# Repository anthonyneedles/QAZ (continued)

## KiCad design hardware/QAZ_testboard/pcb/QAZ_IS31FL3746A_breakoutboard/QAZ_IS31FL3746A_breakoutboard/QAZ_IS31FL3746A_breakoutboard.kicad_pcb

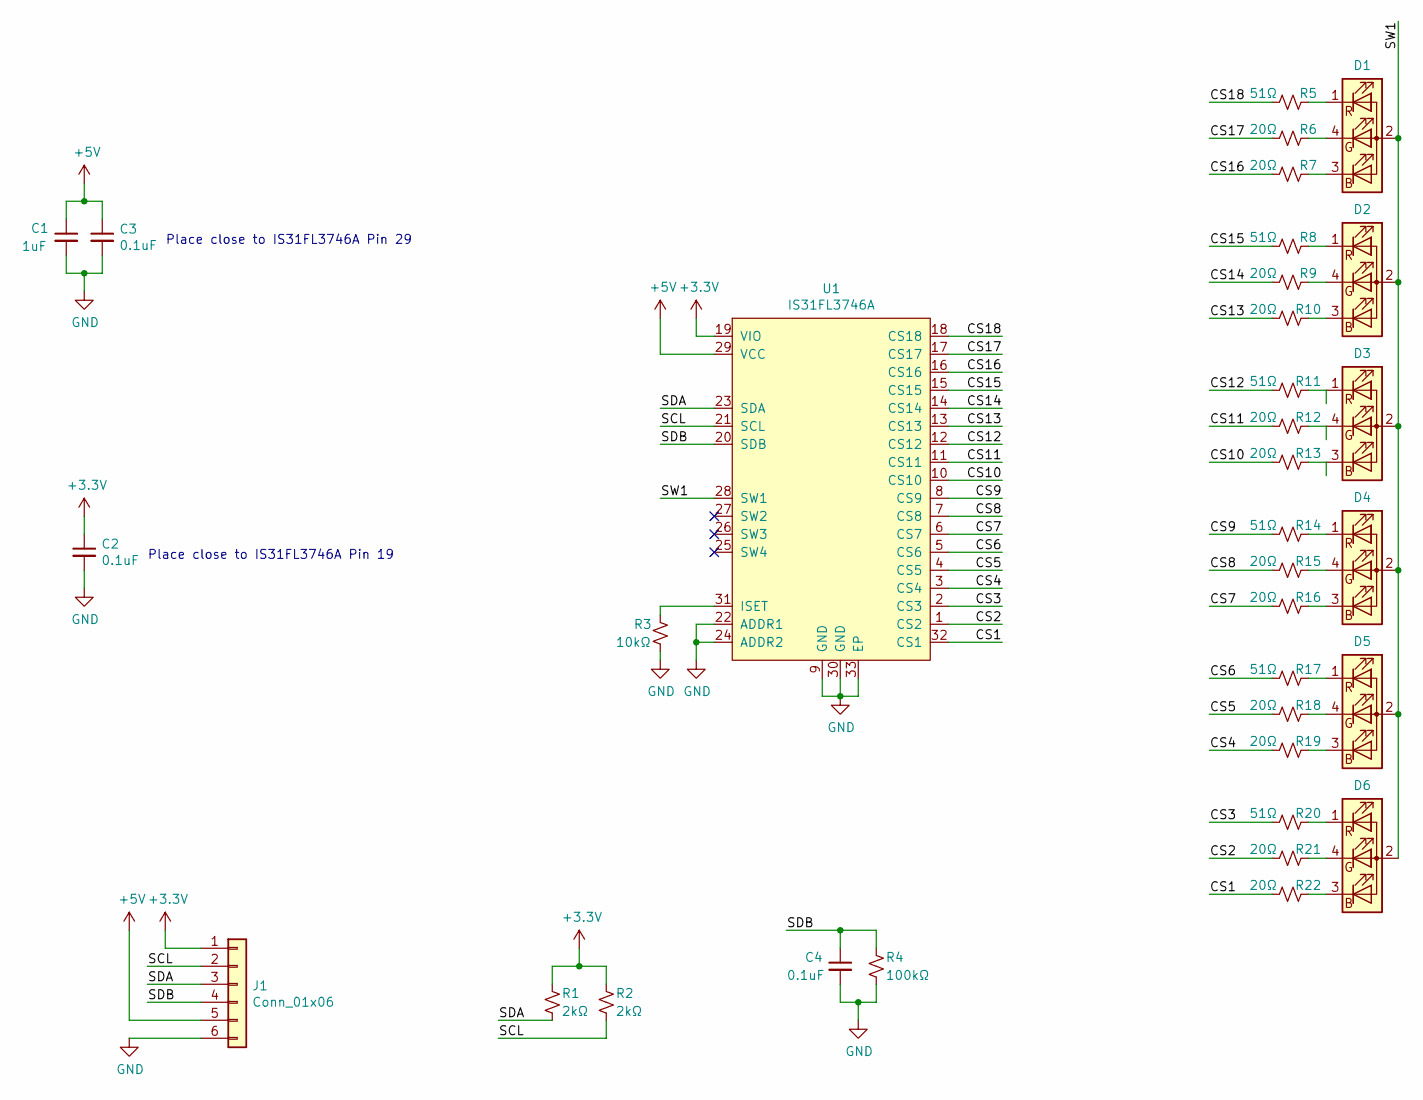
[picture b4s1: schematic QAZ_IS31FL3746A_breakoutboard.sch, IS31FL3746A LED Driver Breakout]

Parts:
C1: 1uF; C_0603_1608Metric_Pad1.05x0.95mm_HandSolder
C2, C3, C4: 0.1uF; C_0603_1608Metric_Pad1.05x0.95mm_HandSolder
D1, D2, D3, D4, D5, D6: LED_ARGB; LED_D5.0mm-4_RGB
J1: Conn_01x06; PinHeader_1x06_P2.54mm_Vertical
R1, R2: 2kΩ; R_0603_1608Metric_Pad1.05x0.95mm_HandSolder
R3: 10kΩ; R_0603_1608Metric_Pad1.05x0.95mm_HandSolder
R4: 100kΩ; R_0603_1608Metric_Pad1.05x0.95mm_HandSolder
R5, R8, R11, R14, R17, R20: 51Ω; R_0603_1608Metric_Pad1.05x0.95mm_HandSolder
R6, R7, R9, R10, R12, R13, R15, R16, R18, R19, R21, R22: 20Ω; R_0603_1608Metric_Pad1.05x0.95mm_HandSolder
U1: IS31FL3746A; QFN-32-1EP_4x4mm_P0.4mm_EP2.9x2.9mm_HS

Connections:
+3V3: C2.1, J1.1, R1.1, R2.1, U1.19 (VIO)
+5V: C1.1, C3.1, J1.5, U1.29 (VCC)
/CS1: R22.2, U1.32 (CS1)
/CS2: R21.2, U1.1 (CS2)
/CS3: R20.2, U1.2 (CS3)
/CS4: R19.2, U1.3 (CS4)
/CS5: R18.2, U1.4 (CS5)
/CS6: R17.2, U1.5 (CS6)
/CS7: R16.2, U1.6 (CS7)
/CS8: R15.2, U1.7 (CS8)
/CS9: R14.2, U1.8 (CS9)
/CS10: R13.2, U1.10 (CS10)
/CS11: R12.2, U1.11 (CS11)
/CS12: R11.2, U1.12 (CS12)
/CS13: R10.2, U1.13 (CS13)
/CS14: R9.2, U1.14 (CS14)
/CS15: R8.2, U1.15 (CS15)
/CS16: R7.2, U1.16 (CS16)
/CS17: R6.2, U1.17 (CS17)
/CS18: R5.2, U1.18 (CS18)
/SCL: J1.2, R2.2, U1.21 (SCL)
/SDA: J1.3, R1.2, U1.23 (SDA)
/SDB: C4.1, J1.4, R4.1, U1.20 (SDB)
/SW1: D1.2 (A), D2.2 (A), D3.2 (A), D4.2 (A), D5.2 (A), D6.2 (A), U1.28 (SW1)
GND: C1.2, C2.2, C3.2, C4.2, J1.6, R3.2, R4.2, U1.9 (GND), U1.22 (ADDR1), U1.24 (ADDR2), U1.30 (GND), U1.33 (EP)
unnamed: D1.1 (RK), R5.1
unnamed: D1.3 (BK), R7.1
unnamed: D1.4 (GK), R6.1
unnamed: D2.1 (RK), R8.1
unnamed: D2.3 (BK), R10.1
unnamed: D2.4 (GK), R9.1
unnamed: D3.1 (RK), R11.1
unnamed: D3.3 (BK), R13.1
unnamed: D3.4 (GK), R12.1
unnamed: D4.1 (RK), R14.1
unnamed: D4.3 (BK), R16.1
unnamed: D4.4 (GK), R15.1
unnamed: D5.1 (RK), R17.1
unnamed: D5.3 (BK), R19.1
unnamed: D5.4 (GK), R18.1
unnamed: D6.1 (RK), R20.1
unnamed: D6.3 (BK), R22.1
unnamed: D6.4 (GK), R21.1
unnamed: R3.1, U1.31 (ISET)

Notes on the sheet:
Place close to IS31FL3746A Pin 29
Place close to IS31FL3746A Pin 19

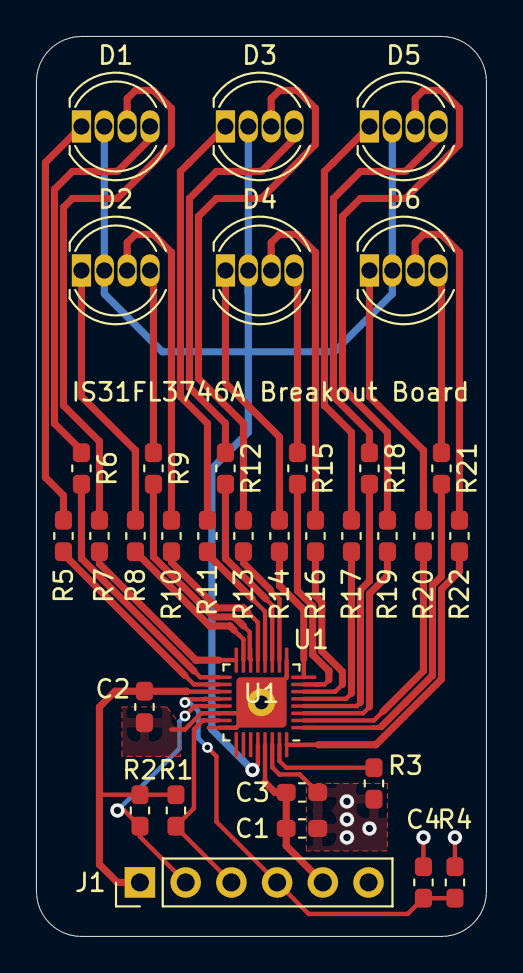
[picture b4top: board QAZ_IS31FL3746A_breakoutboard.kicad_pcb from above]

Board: 2 copper layers, 25.0 x 50.0 mm, 34 parts (0 on the bottom side), 44 nets.

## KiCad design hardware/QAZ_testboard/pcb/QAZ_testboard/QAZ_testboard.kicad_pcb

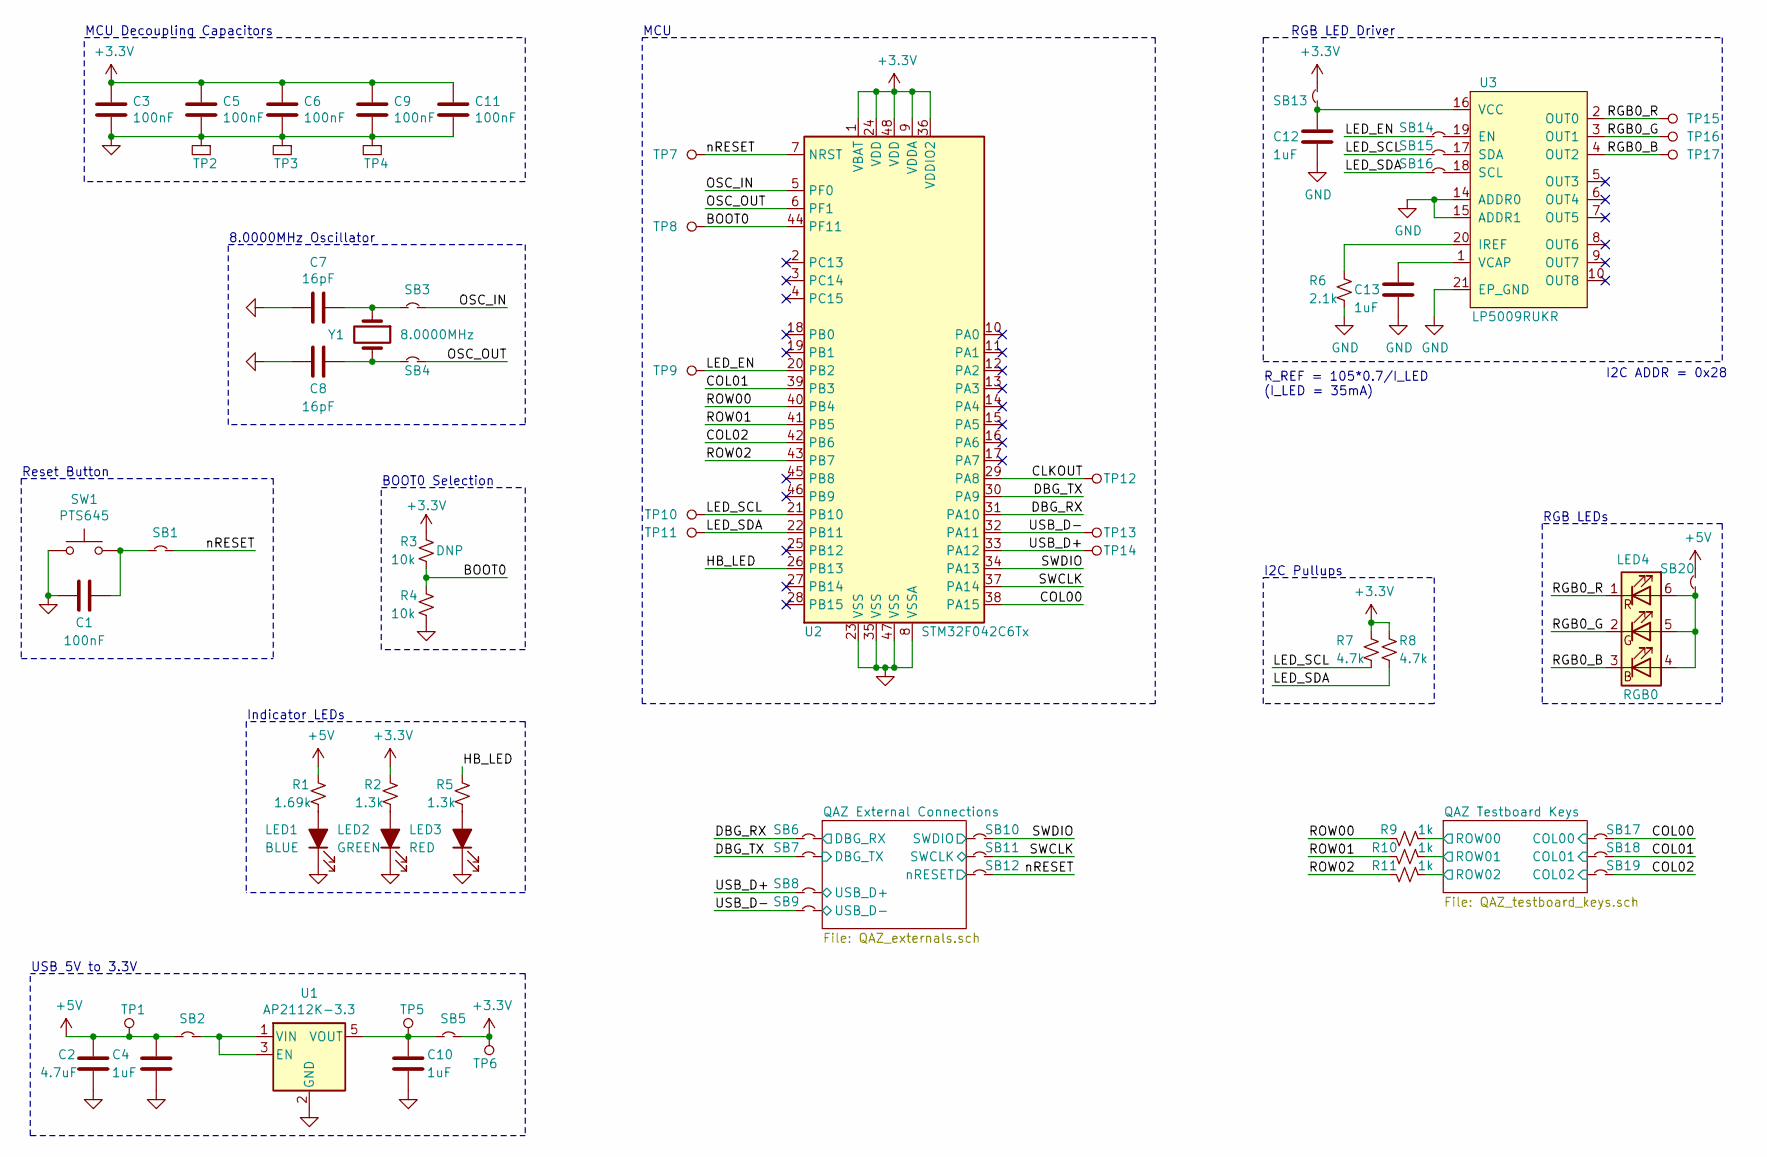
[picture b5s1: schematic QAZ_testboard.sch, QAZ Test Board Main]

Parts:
C1, C3, C5, C6, C9, C11: 100nF; C_0603_1608Metric_Pad1.05x0.95mm_HandSolder
C2: 4.7uF; C_0805_2012Metric_Pad1.15x1.40mm_HandSolder
C4, C10, C12, C13: 1uF; C_0603_1608Metric_Pad1.05x0.95mm_HandSolder
C7, C8: 16pF; C_0603_1608Metric_Pad1.05x0.95mm_HandSolder
LED1: BLUE; R_0603_1608Metric_Pad1.05x0.95mm_HandSolder
LED2: GREEN; R_0603_1608Metric_Pad1.05x0.95mm_HandSolder
LED3: RED; R_0603_1608Metric_Pad1.05x0.95mm_HandSolder
LED4: RGB0; LED_RGB_PLCC-6
R1: 1.69k; R_0603_1608Metric_Pad1.05x0.95mm_HandSolder
R2, R5: 1.3k; R_0603_1608Metric_Pad1.05x0.95mm_HandSolder
R3, R4: 10k; R_0603_1608Metric_Pad1.05x0.95mm_HandSolder
R6: 2.1k; R_0603_1608Metric_Pad1.05x0.95mm_HandSolder
R7, R8: 4.7k; R_0603_1608Metric_Pad1.05x0.95mm_HandSolder
R9, R10, R11: 1k; R_0603_1608Metric_Pad1.05x0.95mm_HandSolder
SB1, SB2, SB3, SB4, SB5, SB6, SB7, SB8, SB9, SB10, SB11, SB12, SB13, SB14, SB15, SB16, SB17, SB18, SB19, SB20: SolderBridge; R_0603_1608Metric_Pad1.05x0.95mm_HandSolder
SW1: PTS645; SW_SPST_PTS645
TP1, TP5, TP6, TP7, TP8, TP9, TP10, TP11, TP12, TP13, TP14, TP15, TP16, TP17: TestPoint; TestPoint_Thruhole_0.7mm
TP2, TP3, TP4: TestPoint_SMD_1812; TestPoint_SMD_1812_HS
U1: AP2112K-3.3; SOT-23-5
U2: STM32F042C6Tx; LQFP-48_7x7mm_P0.5mm
U3: LP5009RUKR; QFN-20-1EP_3x3mm_P0.4mm_EP1.65x1.65mm_HS
Y1: 8.0000MHz; Crystal_SMD_Abracon_ABM7-2Pin_6.0x3.5mm_HS

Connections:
+3V3: C3.2, C5.2, C6.2, C9.2, C11.2, R2.2, R3.2, R7.2, R8.2, SB5.2, SB13.2, TP6.1, U2.1 (VBAT), U2.9 (VDDA), U2.24 (VDD), U2.36 (VDDIO2), U2.48 (VDD); also elsewhere on the board
+5V: C2.2, C4.2, R1.2, SB2.1, SB20.2, TP1.1; also elsewhere on the board
/BOOT0: R3.1, R4.2, TP8.1, U2.44 (PF11)
/CLKOUT: TP12.1, U2.29 (PA8)
/COL00: SB17.2, U2.38 (PA15)
/COL01: SB18.2, U2.39 (PB3)
/COL02: SB19.2, U2.42 (PB6)
/DBG_RX: SB6.1, U2.31 (PA10)
/DBG_TX: SB7.1, U2.30 (PA9)
/HB_LED: R5.2, U2.26 (PB13)
/LED_EN: SB14.1, TP9.1, U2.20 (PB2)
/LED_SCL: R7.1, SB15.1, TP10.1, U2.21 (PB10)
/LED_SDA: R8.1, SB16.1, TP11.1, U2.22 (PB11)
/OSC_IN: SB3.2, U2.5 (PF0)
/OSC_OUT: SB4.2, U2.6 (PF1)
/QAZ External Connections/DBG_RX: SB6.2; also elsewhere on the board
/QAZ External Connections/DBG_TX: SB7.2; also elsewhere on the board
/QAZ External Connections/SWCLK: SB11.1; also elsewhere on the board
/QAZ External Connections/SWDIO: SB10.1; also elsewhere on the board
/QAZ External Connections/USB_D+: SB8.1; also elsewhere on the board
/QAZ External Connections/USB_D-: SB9.1; also elsewhere on the board
/QAZ External Connections/nRESET: SB12.2; also elsewhere on the board
/QAZ Testboard Keys/COL00: SB17.1; also elsewhere on the board
/QAZ Testboard Keys/COL01: SB18.1; also elsewhere on the board
/QAZ Testboard Keys/COL02: SB19.1; also elsewhere on the board
/QAZ Testboard Keys/ROW00: R9.1; also elsewhere on the board
/QAZ Testboard Keys/ROW01: R10.1; also elsewhere on the board
/QAZ Testboard Keys/ROW02: R11.1; also elsewhere on the board
/RGB0_B: LED4.3 (BK), TP17.1, U3.4 (OUT2)
/RGB0_G: LED4.2 (GK), TP16.1, U3.3 (OUT1)
/RGB0_R: LED4.1 (RK), TP15.1, U3.2 (OUT0)
/ROW00: R9.2, U2.40 (PB4)
/ROW01: R10.2, U2.41 (PB5)
/ROW02: R11.2, U2.43 (PB7)
/SWCLK: SB11.2, U2.37 (PA14)
/SWDIO: SB10.2, U2.34 (PA13)
/USB_D+: SB8.2, TP14.1, U2.33 (PA12)
/USB_D-: SB9.2, TP13.1, U2.32 (PA11)
/nRESET: SB1.2, SB12.1, TP7.1, U2.7 (NRST)
GND: C1.1, C2.1, C3.1, C4.1, C5.1, C6.1, C7.2, C8.2, C9.1, C10.1, C11.1, C12.1, C13.1, LED1.1 (K), LED2.1 (K), LED3.1 (K), R4.1, R6.1, SW1.1, TP2.1, TP3.1, TP4.1, U1.2 (GND), U2.8 (VSSA), U2.23 (VSS), U2.35 (VSS), U2.47 (VSS), U3.14 (ADDR0), U3.15 (ADDR1), U3.21 (EP_GND); also elsewhere on the board
unnamed: C1.2, SB1.1, SW1.2
unnamed: C7.1, SB3.1, Y1.1
unnamed: C8.1, SB4.1, Y1.2
unnamed: C10.2, SB5.1, TP5.1, U1.5 (VOUT)
unnamed: C12.2, SB13.1, U3.16 (VCC)
unnamed: C13.2, U3.1 (VCAP)
unnamed: LED1.2 (A), R1.1
unnamed: LED2.2 (A), R2.1
unnamed: LED3.2 (A), R5.1
unnamed: LED4.4 (BA), LED4.5 (GA), LED4.6 (RA), SB20.1
unnamed: R6.2, U3.20 (IREF)
unnamed: SB2.2, U1.1 (VIN), U1.3 (EN)
unnamed: SB14.2, U3.19 (EN)
unnamed: SB15.2, U3.17 (SDA)
unnamed: SB16.2, U3.18 (SCL)

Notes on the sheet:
USB 5V to 3.3V
MCU Decoupling Capacitors
Reset Button
8.0000MHz Oscillator
BOOT0 Selection
MCU
Indicator LEDs
RGB LEDs
R_REF = 105*0.7/I_LED (I_LED = 35mA)
I2C Pullups
I2C ADDR = 0x28
RGB LED Driver

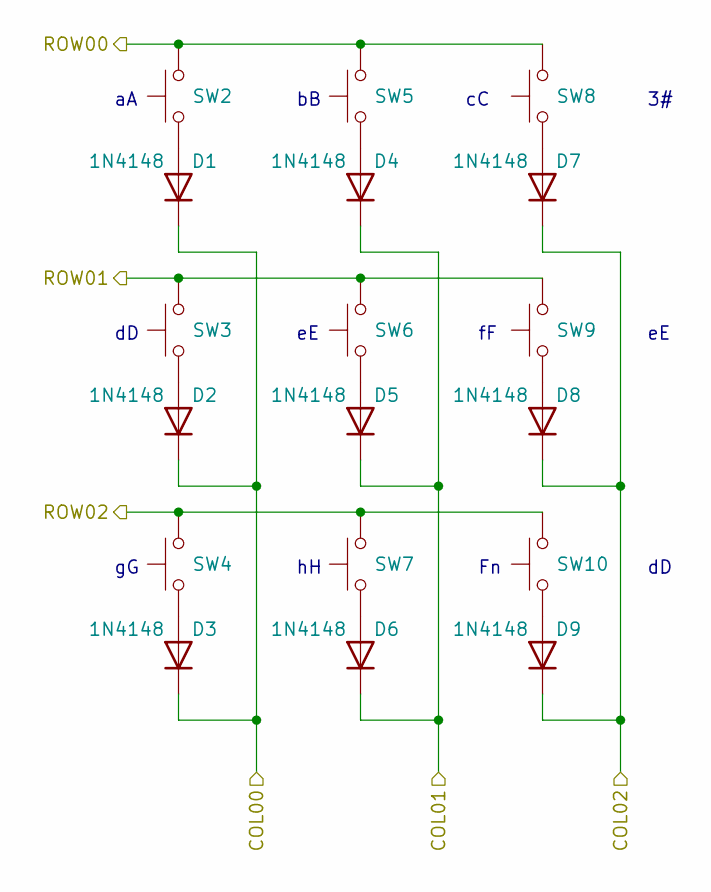
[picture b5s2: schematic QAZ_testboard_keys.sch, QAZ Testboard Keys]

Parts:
D1, D2, D3, D4, D5, D6, D7, D8, D9: 1N4148; D_DO-35_SOD27_P7.62mm_Horizontal
SW2, SW3, SW4, SW5, SW6, SW7, SW8, SW9, SW10: Cherry MX; SW_Cherry_MX_1.00u_PCB

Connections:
/QAZ Testboard Keys/COL00: D1.1 (K), D2.1 (K), D3.1 (K); also elsewhere on the board
/QAZ Testboard Keys/COL01: D4.1 (K), D5.1 (K), D6.1 (K); also elsewhere on the board
/QAZ Testboard Keys/COL02: D7.1 (K), D8.1 (K), D9.1 (K); also elsewhere on the board
/QAZ Testboard Keys/ROW00: SW2.2, SW5.2, SW8.2; also elsewhere on the board
/QAZ Testboard Keys/ROW01: SW3.2, SW6.2, SW9.2; also elsewhere on the board
/QAZ Testboard Keys/ROW02: SW4.2, SW7.2, SW10.2; also elsewhere on the board
unnamed: D1.2 (A), SW2.1
unnamed: D2.2 (A), SW3.1
unnamed: D3.2 (A), SW4.1
unnamed: D4.2 (A), SW5.1
unnamed: D5.2 (A), SW6.1
unnamed: D6.2 (A), SW7.1
unnamed: D7.2 (A), SW8.1
unnamed: D8.2 (A), SW9.1
unnamed: D9.2 (A), SW10.1

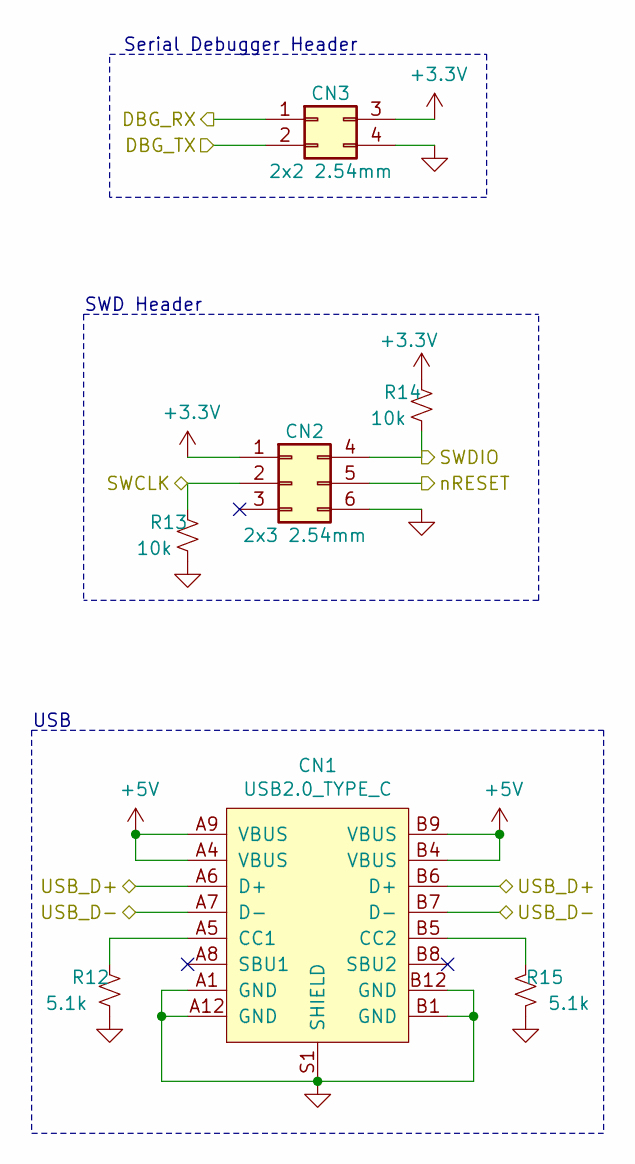
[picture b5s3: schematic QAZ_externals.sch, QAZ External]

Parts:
CN1: USB2.0_TYPE_C; USB_C_GCT_USB4085
CN2: 2x3 2.54mm; PinHeader_2x03_P2.54mm_Vertical
CN3: 2x2 2.54mm; PinHeader_2x02_P2.54mm_Vertical
R12, R15: 5.1k; R_0603_1608Metric_Pad1.05x0.95mm_HandSolder
R13, R14: 10k; R_0603_1608Metric_Pad1.05x0.95mm_HandSolder

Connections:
+3V3: CN2.1, CN3.3, R14.2; also elsewhere on the board
+5V: CN1.A4 (VBUS), CN1.A9 (VBUS), CN1.B4 (VBUS), CN1.B9 (VBUS); also elsewhere on the board
/QAZ External Connections/DBG_RX: CN3.1; also elsewhere on the board
/QAZ External Connections/DBG_TX: CN3.2; also elsewhere on the board
/QAZ External Connections/SWCLK: CN2.2, R13.2; also elsewhere on the board
/QAZ External Connections/SWDIO: CN2.4, R14.1; also elsewhere on the board
/QAZ External Connections/USB_D+: CN1.A6 (D+), CN1.B6 (D+); also elsewhere on the board
/QAZ External Connections/USB_D-: CN1.A7 (D-), CN1.B7 (D-); also elsewhere on the board
/QAZ External Connections/nRESET: CN2.5; also elsewhere on the board
GND: CN1.A1 (GND), CN1.A12 (GND), CN1.B1 (GND), CN1.B12 (GND), CN1.S1 (SHIELD), CN2.6, CN3.4, R12.1, R13.1, R15.1; also elsewhere on the board
unnamed: CN1.A5 (CC1), R12.2
unnamed: CN1.B5 (CC2), R15.2

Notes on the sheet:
SWD Header
Serial Debugger Header
USB

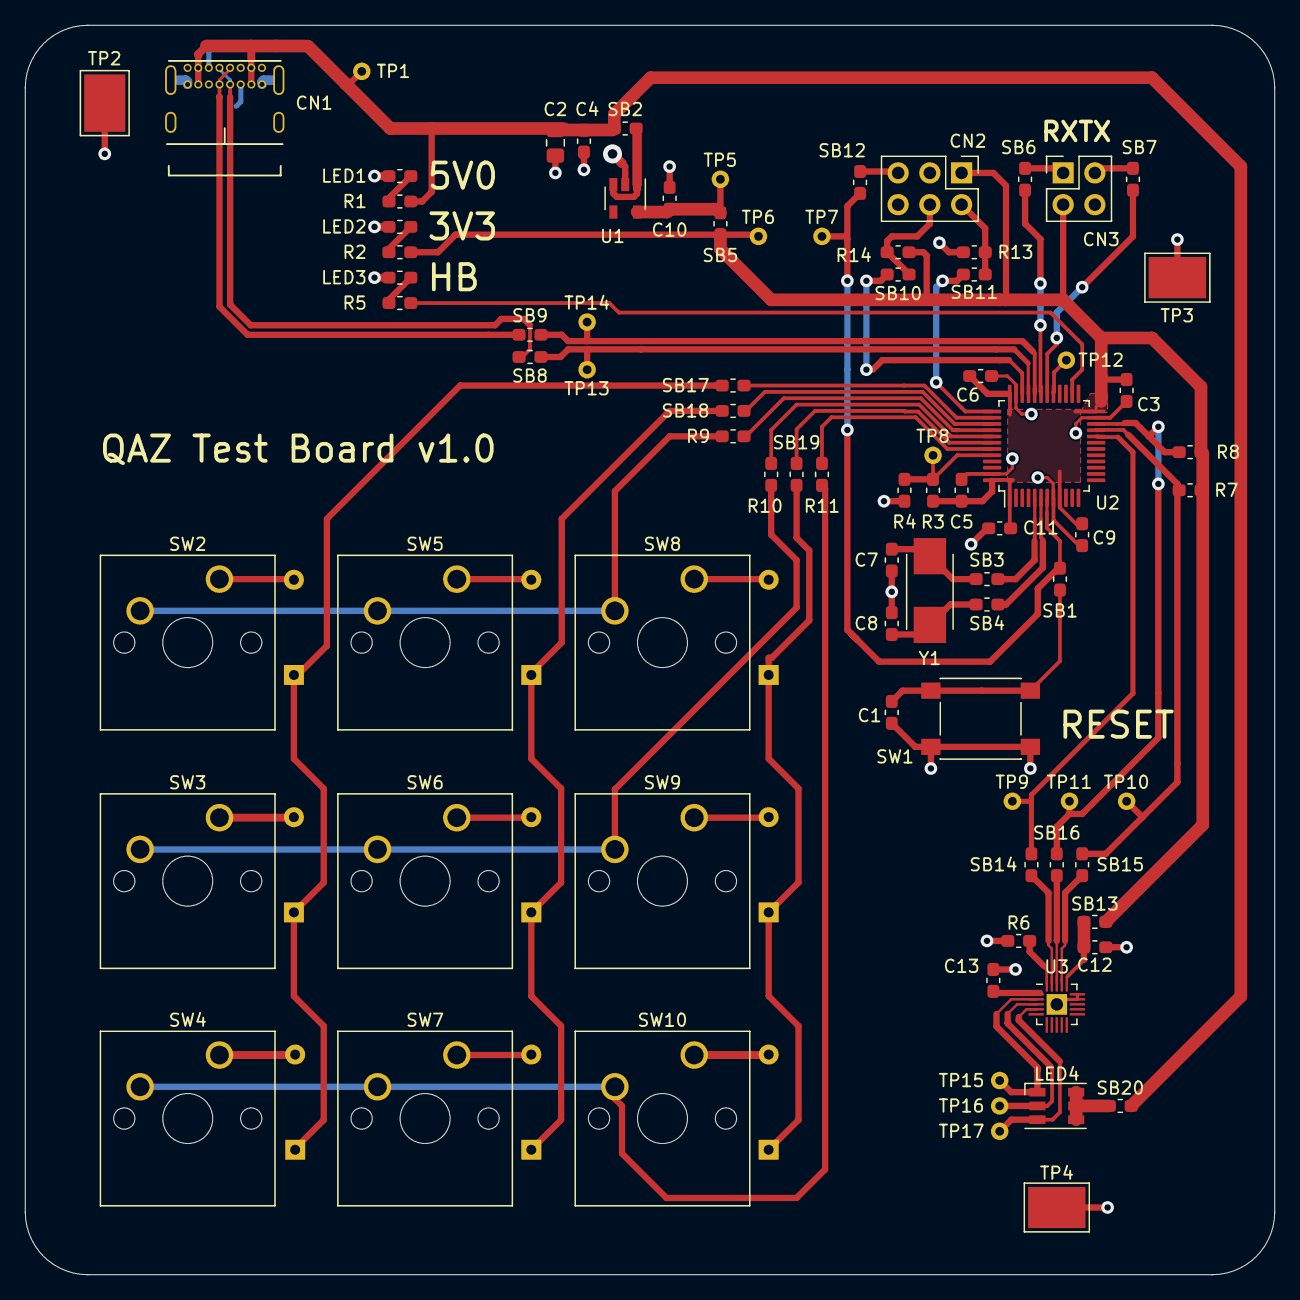
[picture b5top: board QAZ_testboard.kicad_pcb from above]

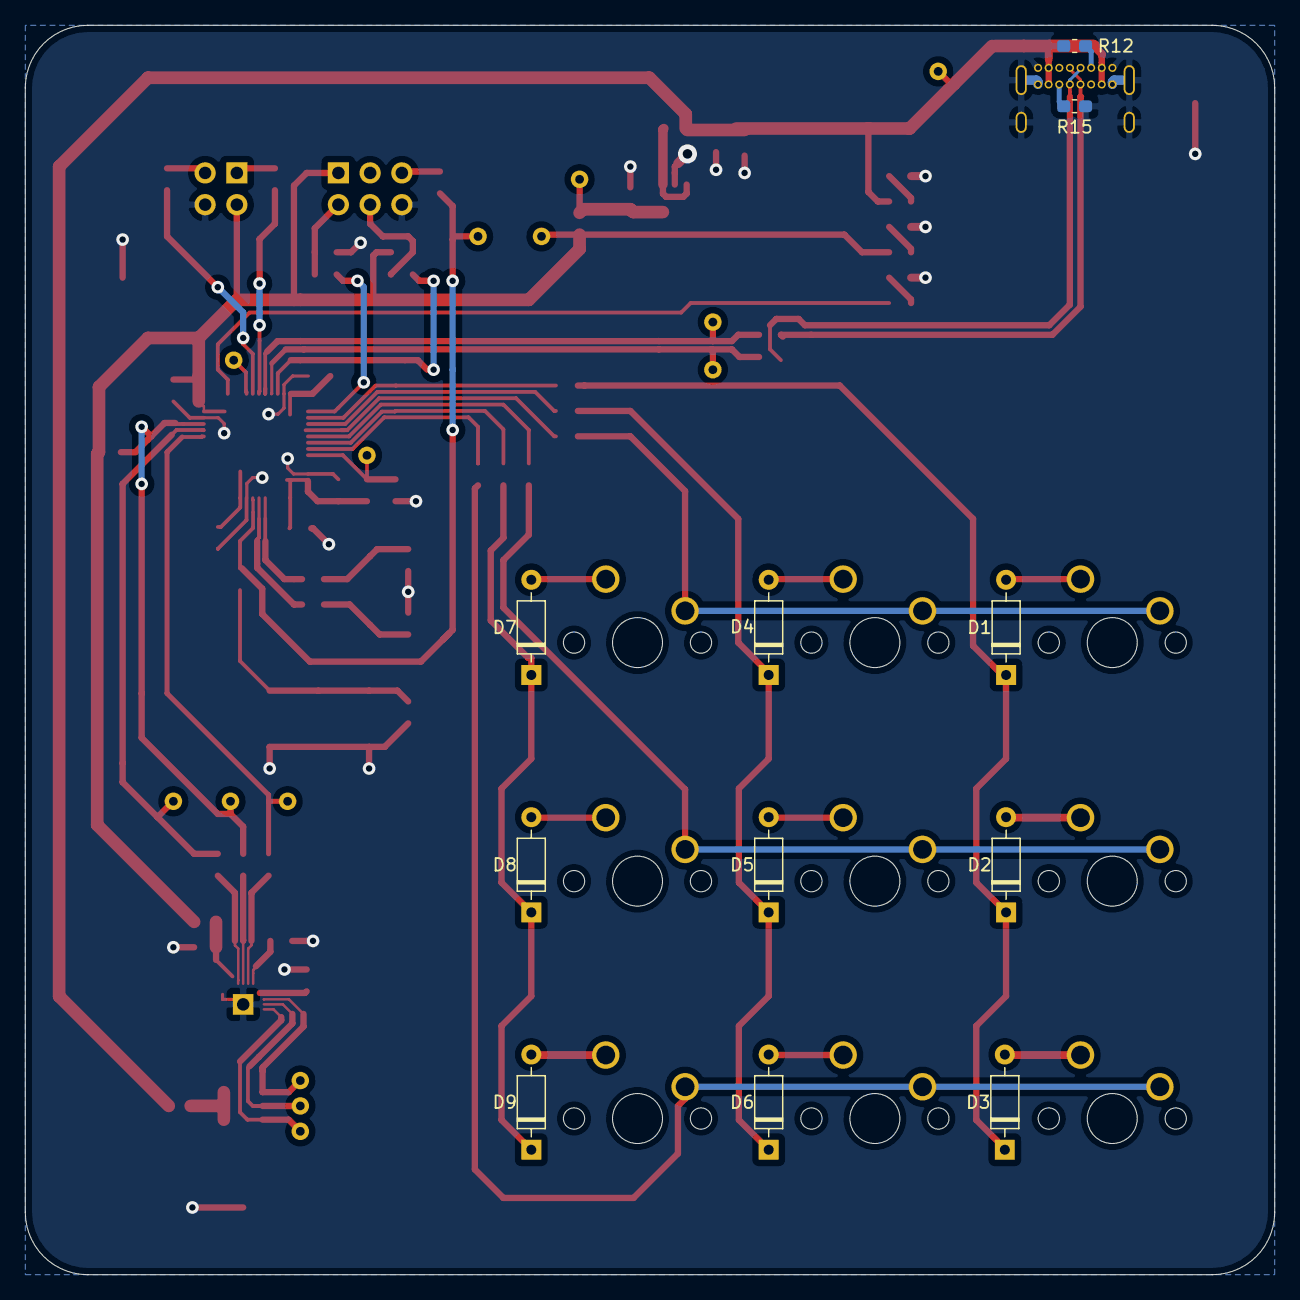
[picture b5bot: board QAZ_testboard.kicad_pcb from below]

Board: 2 copper layers, 100.0 x 100.0 mm, 95 parts (11 on the bottom side), 66 nets.

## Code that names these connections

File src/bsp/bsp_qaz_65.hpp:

/**
 * @file      bsp_qaz_65.hpp
 * @brief     BSP for the QAZ 65% board
 *
 * @author    Anthony Needles
 * @date      2020/12/20
 * @copyright (c) 2020 Anthony Needles. GNU GPL v3 (see LICENSE)
 *
 * Definitions specfic to the QAZ 65% board.
 */

#ifndef BSP_BSP_QAZ_65_HPP_
#define BSP_BSP_QAZ_65_HPP_

#include "core/gpio.hpp"

/**
 * @brief Board support package namespace (for QAZ 65% board)
 *
 * This namespace holds definitions specific to a certain QAZ board.
 *
 * Is this the correct way to use the term "BSP"? Eh...
 */
namespace bsp {

// individual gpio pins
constexpr gpio::Id HB_LED  = { gpio::B, gpio::PIN_0  };
constexpr gpio::Id MCO     = { gpio::A, gpio::PIN_8  };
constexpr gpio::Id DBG_TX  = { gpio::A, gpio::PIN_9  };
constexpr gpio::Id RGB_EN  = { gpio::B, gpio::PIN_2  };
constexpr gpio::Id RGB_SDA = { gpio::B, gpio::PIN_11 };
constexpr gpio::Id RGB_SCL = { gpio::B, gpio::PIN_10 };

/// Key matrix column gpio pins
constexpr gpio::Id COLS[] = {
    { gpio::C, gpio::PIN_13 },  // COL00
    { gpio::C, gpio::PIN_14 },  // COL01
    { gpio::C, gpio::PIN_15 },  // COL02
    { gpio::B, gpio::PIN_12 },  // COL03
    { gpio::B, gpio::PIN_13 },  // COL04
    { gpio::B, gpio::PIN_14 },  // COL05
    { gpio::B, gpio::PIN_15 },  // COL06
    { gpio::A, gpio::PIN_10 },  // COL07
    { gpio::A, gpio::PIN_15 },  // COL08
    { gpio::B, gpio::PIN_3  },  // COL09
    { gpio::B, gpio::PIN_4  },  // COL10
    { gpio::B, gpio::PIN_5  },  // COL11
    { gpio::B, gpio::PIN_6  },  // COL12
    { gpio::B, gpio::PIN_7  },  // COL13
    { gpio::B, gpio::PIN_8  },  // COL14
};

/// Key matrix row gpio pins
constexpr gpio::Id ROWS[] = {
    { gpio::A, gpio::PIN_1  },  // ROW00
    { gpio::A, gpio::PIN_2  },  // ROW01
    { gpio::A, gpio::PIN_3  },  // ROW02
    { gpio::A, gpio::PIN_4  },  // ROW03
    { gpio::A, gpio::PIN_0  },  // ROW04
};

}  // namespace bsp

/// Base key symbol table
///     symbol - the symbol for the key. must match with HID_USAGE_KEYBOARD_* define
#define BASE_TABLE(K) \
    K(ESC)   K(1)     K(2)     K(3)     K(4)     K(5)     K(6)     K(7)     K(8)     K(9)     K(0)     K(DASH)  K(EQUAL) K(BKSPC) K(GRAVE)  /* NOLINT */  \
    K(TAB)   K(Q)     K(W)     K(E)     K(R)     K(T)     K(Y)     K(U)     K(I)     K(O)     K(P)     K(LBRKT) K(RBRKT) K(BSLSH) K(PGEUP)  /* NOLINT */  \
    K(CPLCK) K(A)     K(S)     K(D)     K(F)     K(G)     K(H)     K(J)     K(K)     K(L)     K(SEMI)  K(QUOTE) K(NONE)  K(ENTER) K(PGEDN)  /* NOLINT */  \
    K(LSHFT) K(Z)     K(X)     K(C)     K(V)     K(B)     K(N)     K(M)     K(COMMA) K(PRIOD) K(FSLSH) K(RSHFT) K(NONE)  K(UARRW) K(DELET)  /* NOLINT */  \
    K(LCTRL) K(LGUI)  K(LALT)  K(NONE)  K(NONE)  K(SPACE) K(NONE)  K(NONE)  K(RALT)  K(FN)    K(RCTRL) K(LARRW) K(NONE)  K(DARRW) K(RARRW)  /* NOLINT */

/// Fn key symbol table - for when the FN key is pressed
///     symbol - the symbol for the key. must match with HID_USAGE_KEYBOARD_* define
#define FN_TABLE(K) \
    K(NONE)  K(F1)    K(F2)    K(F3)    K(F4)    K(F5)    K(F6)    K(F7)    K(F8)    K(F9)    K(F10)   K(F11)   K(F12)   K(NONE)  K(PROF)   /* NOLINT */ \
    K(NONE)  K(NONE)  K(NONE)  K(NONE)  K(NONE)  K(NONE)  K(NONE)  K(NONE)  K(NONE)  K(NONE)  K(NONE)  K(NONE)  K(NONE)  K(NONE)  K(BRTUP)  /* NOLINT */ \
    K(NONE)  K(NONE)  K(NONE)  K(NONE)  K(NONE)  K(NONE)  K(NONE)  K(NONE)  K(NONE)  K(NONE)  K(NONE)  K(NONE)  K(NONE)  K(NONE)  K(BRTDN)  /* NOLINT */ \
    K(NONE)  K(NONE)  K(NONE)  K(NONE)  K(NONE)  K(NONE)  K(NONE)  K(NONE)  K(NONE)  K(NONE)  K(NONE)  K(NONE)  K(NONE)  K(VOLUP) K(COLOR)  /* NOLINT */ \
    K(LCTRL) K(LGUI)  K(LALT)  K(NONE)  K(NONE)  K(NONE)  K(NONE)  K(NONE)  K(RALT)  K(FN)    K(RCTRL) K(SPDDN) K(NONE)  K(VOLDN) K(SPDUP)  /* NOLINT */

/// Which keys get a callback function
#define CALLBACK_KEY_TABLE(K) \
    K(BRTUP) K(BRTDN) K(COLOR) K(PROF) K(SPDUP) K(SPDDN)

/// USART used for sending debug messages
#define DEBUG_UART    USART1

/// I2C used for talking to the LED controller
#define RGB_LED_I2C   I2C1

#endif  // BSP_BSP_QAZ_65_HPP_

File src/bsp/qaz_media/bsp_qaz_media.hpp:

/**
 * @file      bsp_qaz_media.hpp
 * @brief     BSP for the QAZ Media board
 *
 * @author    Anthony Needles
 * @date      2021/06/24
 * @copyright (c) 2020 Anthony Needles. GNU GPL v3 (see LICENSE)
 *
 * Definitions specfic to the QAZ Media board.
 */

#if !defined(BSP_BSP_HPP_)

#error Do not include board BSP header directly, please include bsp.hpp

#endif

#ifndef BSP_QAZ_MEDIA_BSP_QAZ_MEDIA_HPP_
#define BSP_QAZ_MEDIA_BSP_QAZ_MEDIA_HPP_

#include "core/gpio.hpp"

/**
 * @brief Board support package namespace (for QAZ Media board)
 *
 * This namespace holds definitions specific to a certain QAZ board.
 *
 * Is this the correct way to use the term "BSP"? Eh...
 */
namespace bsp {

// individual gpio pins
constexpr gpio::Id HB_LED    = { gpio::A, gpio::PIN_5  };
constexpr gpio::Id MCO       = { gpio::A, gpio::PIN_8  };
constexpr gpio::Id DBG_TX    = { gpio::A, gpio::PIN_9  };
constexpr gpio::Id MUTE_LED  = { gpio::A, gpio::PIN_3  };
constexpr gpio::Id ROT_ENC_A = { gpio::B, gpio::PIN_5  };
constexpr gpio::Id ROT_ENC_B = { gpio::B, gpio::PIN_4  };

// An Id for each button
enum ButtonId {
    STOP        = 0,
    PREVIOUS    = 1,
    PLAY_PAUSE  = 2,
    NEXT        = 3,
    MUTE        = 4,
};

/// Button gpio pins
constexpr gpio::Id BUTTONS[] = {
    { gpio::B, gpio::PIN_1  },  // STOP
    { gpio::B, gpio::PIN_2  },  // PREVIOUS
    { gpio::B, gpio::PIN_10 },  // PLAY/PAUSE
    { gpio::B, gpio::PIN_11 },  // NEXT
    { gpio::A, gpio::PIN_15 },  // MUTE
};

/// bsp-specific initializations
void init(void);

}  // namespace bsp

/// USART used for sending debug messages
#define DEBUG_UART USART1

#endif  // BSP_QAZ_MEDIA_BSP_QAZ_MEDIA_HPP_

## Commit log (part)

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2020-09-14 init: set up project framework
2020-09-27 testboard: sch/pcb design for test board
    The QAZ Test Board will be used for checkout hardware and development of
    software. It features a 3x3 switch matrix, 1 RGB LED (w/ driver), SWD
    connection, debug UART connection, 5V to 3.3V regulator, USB Type-C
    connector, external crystal, STM32F042K6.
2020-10-16 testboard: added debug uart
    Since using printf would require too much memory, DbgPrintf was defined
    as an alternative. This works very similar, but without some features.
    It will print over the debug uart USART1 @ PA8.
    Using assert would also require too much memory, so DBG_ASSERT was
    defined to give the same functionality. If the expression is false, then
    the context/expression is printed and the program halts.
2020-10-18 testboard: add i2c module
    Added i2c module for driving I2C1. This will be used for communicating
    with the RGB LED driver.
2020-10-31 rgb_led: adding rgb led driver
    Adding RGB LED driver that will utilize the I2C driver to communicate
    with the LP5009 LED driver. The driver is put into bank mode, which
    means that all LEDs are driven with the same values. API gives functions
    to set the brightness and color.
2020-11-03 tmux/readme: add tmux bootstrap and readme update
    Added tmux bootstrap to create a QAZ session.
    Updated readme.
2020-11-16 usb: added usb driver
    The USB driver will hold the API for directly interacting with the USB
    peripheral. For our purposes, we only use EP0 as TX/RX control, and EP1
    as interrupt tx.
    The QAZ USB device get successfully recognized on a machine running
    Debian (all descriptors are obtained by host), but the transmission of
    data has yet to be developed.
2020-11-17 qaz-65: add layer .svg files
2020-11-22 qaz_65: updated for qaz 65% bsp
2020-11-26 usb: finally past enumeration, sending reports
    Finally got the device full enumerated and sending reports to the host.
    Since the device is defined as a mouse, we are sending cursor move
    reports, which successfully occur on the pc.
    The problem was not realizing that in the EP_REG macro I was incremented
    double the amount I wanted because of pointer arithmetic.
    Now, we can fine tune our actual keyboard report descriptor and start
2020-11-26 refactor: renamed variables/functions
    For naming consistency...
2020-12-07 bugfix: fixed modifier keys
    The left modifier keys would be setting the right modifier fields in the
    report.
2020-12-21 bsp: added qaz_65/testboard bsp
    This allows easily switching the board type with a Makefile user
    variable change.
2020-12-21 uart: split debug/uart
    In an effor to further modualize source files, the UART portions of the
    debug module were moved to their own separate file set (which itself is
    located in the comms/ subdir).
    Also fixed some indentation issues.
2020-12-24 cpplint: added cpplinter.py
    `make lint` will now run cpplint.py on all source files. There are a few
    checking exclusions, and line length is set to 100.
    Made appropriate changes to the code so that the linter passes.
2020-12-24 docs: added Doxygen config
    Added Doxygen configuration, which is used in `make docs` to create html
    documentation. Cleaned up file headers and function headers to remove
    warnings. license command merged into copyright command.
2020-12-24 qaz v1.1: fixes going from v1.0->v1.1
    Changed from individual pull up/down on BOOT0 MCU pin to switch that can
    easily change from one to the other (without soldering). This is
    required for programming over USB DFU.
    Fixed RESET switch, pins were flipped on part layout.
2020-12-24 doc: updated documentation
2020-12-26 bitops: added bitop macros
    All bit operations are now performed using the bitop macros, to make
    code a little more readable. Also added macros for setting GPIO pins.
    GPIO inits for i2c/uart were moved to their respective application
    modules to abstract away the BSP layer.
2021-01-02 cpp: changing from C to C++
2021-01-02 cpp: added gpio struct template
    In an effort to "convert" this project to C++, there is a now a template
    for a gpio structure, which holds several methods useful to gpios.
    In a pleasant surprise, the code generates the **SAME EXACT CODE** as
    the macros. Wonderful compile-time utilization.
2021-01-03 cpp: bitop class template
    Added class template for performing bitops on a specific type.
    Updated class comments.
2021-01-03 cpp: gpio changes
    The previous implementation of the GPIOBase class would not work well
    with the implementation of the key matrix (in it's current state). So
    the new GPIO struct just contains the GPIO modifier methods, which take
    an ID for each gpio.
    The resultant memory usage is unchanged.
2021-01-04 cpp: bitop changes, no more bitop macros
    An improvement to the bitop module was to "free" the functions and move
    them from the GPIO struct to a gpio namespace. The template type param
    is then automatically deduced when called, depending on the type of `x`.
2021-01-04 cpp: comms/ -> comm/
2021-01-06 cpp: usb hid reenabled
    Incorrectly changed a cast which broke USB. Working now.
2021-01-09 cpp: 'inline'd constexpr global variables
    This doesn't change much for this project due to the optimization level.
    Without '-02' each translation unit that includes a header with
    constexpr constants will create a copy for each TU (internal linkage),
    since constexp does not imply inline for 'global' variables. Thus,
    inline needs to be explicitly given.
2021-01-09 cpp: updated hb module
2021-01-10 commenting: updated commenting methods
    All function headers with params shall have two spaces between the name
    of the param and the description of the param. The params shall be
    grouped together, and there shall be an empty line between params and
    any return.
    All function prototypes shall only have doxygen-style triple-backslash
    headers. The actual definitions of the functions will be commented as
2021-01-10 cpp: updated key matrix
    Updated key matrix for C++
2021-01-10 cpp:: updated usb hid
    Now calling USB HID module KB (keyboard) HID, since it is a very
    specific HID application.
    Updated for C++
2021-01-10 doxygen: suppress warning with __WEAK overrides
    For some reason, Doxygen can't find the declarations of the callback
    functions in the keymatrix namespace from lighting.cpp. This has to do
    with the preprocessor generation, because if I manually write the weak
    function prototype, it works. But preprocessing is enabled for
    Doxygen... oh well.
2021-01-10 readme: updated readme
2021-01-16 idle: add idle detection for lighting
    Count the number of key matrix task loops that detect no key presses.
    After a defined number of loops, the keyboard is considered "idle". The
    lighting task checks this, and if idle, the lighting is turned off
    until the next key press.
2021-01-20 persist: added saving user data in flash
    A user would likely want their color profile persist over PORs of the
    board. In order to do this, config needs to be saved in non-volatile
    memory. Since the program is using less than half (in DEBUG) of the
    available 32kB of Flash, the last two pages (for a total of 2kB) are
    reserved for use with persisting data.
    ST provides an EEPROM emulator which handles page
2021-01-21 exclude: exclude specific files to doxygen/lint
    Instead of just excluding all files except .c/.h files, only specified
    files will be excluded. Excluded files from Doxygen aer specified in
    build/Doxyfile, and from exluded files from cpplint in
    build/clint-excluded-files.txt
2021-04-18 usb: hardcoded fixes
    Removed hardware delays which caused issues depending on the host.
    The fixes are hardcoded, and a larger structural change in the usb
    driver is needed to fully resolve the issues.
2021-04-19 usb: ep control structure
    Add control structure to hold values for each ep, making it easier to
    call generic functions with the ep number as an input.
2021-04-25 usb: IN completion handling
    Add a function that gets called when an IN has completed on ep0. This
    handles changing the device address, as well as anticipating when the
    host will request more data (when sending less data than requested).
2021-05-30 cmake: restructured project building
    In an effort to gain experience using cmake, this project now uses cmake
    (along with a top-level Makefile).
2021-05-30 expr: remove inlines, macros
    There is no real reason to constantly include `inline` to our constexpr
    variables. A constexpr variable is `const`. A non-inline `const`
    variable that is not explicitly declared `extern` has internal
    linkage.
2021-05-30 usb-irq: critical read/write regions
    Since the read/write usb driver methods can be called outside of an IRQ
    context, we should wrap them in a critical region (disabling then
    reenabling USB interrupts) to ensure that no read/writes are interrupted
    in the middle of their process, possibly corrupting data.
2021-05-30 i2c_speed: icreased to fast most, 400kHz
    Since so much time is spent writing to the I2C LED driver, the task can
    actually overrun. Thus, the speed was increased to 400kHz. Additionally,
    to make the slow color/brightness changes more smooth, decrease the task
    period for the lighting (we need to decrease the timeslice period as
    well).
2021-05-30 layers: added v2/v3 layers for qaz 65%
    closes #4
    v2 has slightly altered holes on the top of the outline, since the SWD
    connector is not brought out.
    v3 is for using a pcb as the plate layer (not sure if it will work..)
2021-05-30 cleanup: remove breakout boards
    No need to keep the breakout boards in the repo.
2021-06-02 sidecut: updated sidecut with pcb plate
2021-06-15 qaz-v1.1: updated bsp and readme
    The pinout of v1.1 is slightly different than v1.0, so the bsp was
    updated.
2021-06-15 linker: update to stm32f042c6 linker
    There isn't anything really different, but the name should match the
    actual MCU.
2021-06-24 bom: fixed qaz media v1.0 bom
    Forgot the two 0.01uF caps.
2021-06-25 bsp: splitting of program based on bsp
    Well, this isn't a very good solution but it will work for now.
    I want to be able to easily switch in and out modules based on
    whether a particular board needs it. For example, the QAZ 65%
    needs lighting, the key matrix, and keyboard hid functionality. But the
    QAZ Media board doesn't need these.
    So how do I handle this? In a very non-scalable way. Each BSP has its
2021-06-26 buttons: added buttons debouncing module
    Add button module for QAZ Media that debounces the buttons for use.
2021-06-27 rotary encoder: added reading volume knob
    Using TIM3 CH1 and CH2 the rotary encoder is read.
2021-06-28 consumer: add consumer HID functionality
    The consumer report gets set based on button presses/rotations of the
    rotary encoder.
    The consumer device has different descriptors, so there needs to be a
    split for the keyboard device and the consumer device.
2021-06-28 make: improvements to Makefile
    Add BUILD_TYPE and BOARD printouts when building.
    Added functionality to automatically rebuild the project whenever the
    Makefile is changed, with help of a dummy marker file. Updated docs.
2021-07-19 mute: add mute led toggling
    When the volume knob is pressed, the mute LED will toggle.
    Unfortunately, this isn't really the best use of the LED. The MUTE
    LED should reflect the MUTE state of the machine (which can be changed
    on the computer, as well). However, the state of this LED, as opposed to
    the capslock/numlock/etc LEDs, are not reported by standard
    HID drivers.
2021-08-08 user config: add local user config makefile
    Added a template for a user config makefile that is not actually tracked
    by Git. The user needs to create this file (ideally by copying the
    template) so that these variables can be used when building.
    The reason for making this something not tracked is because we really
    don't want to track these sort of changes, and force stashing/removing
    these changes when committing, since there isn't a "default" build type.
